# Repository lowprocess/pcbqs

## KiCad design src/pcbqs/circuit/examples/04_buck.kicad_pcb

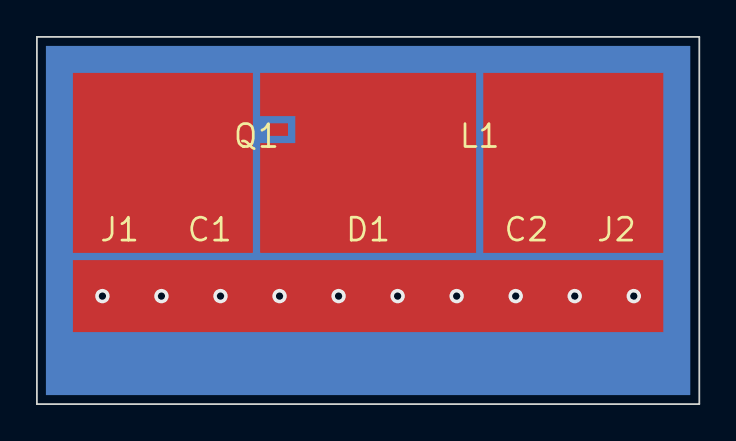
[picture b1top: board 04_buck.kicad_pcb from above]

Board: 2 copper layers, 36.8 x 20.4 mm, 7 parts (0 on the bottom side), 4 nets, no tracks yet.

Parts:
C1: 22u; C_1210_3225Metric
C2: 47u; C_1210_3225Metric
D1: D; D_SMA
J1: supply; SolderWirePad_1x02_SMD_3x3mm
J2: load 2.5; SolderWirePad_1x02_SMD_3x3mm
L1: 22uH; L_7.3x7.3_H4.5
Q1: MOSFET; SO-8FL_5x6mm

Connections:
GND: C1.2, C2.2, D1.2 (A), J1.2, J2.2
in: C1.1, J1.1, Q1.1 (D)
out: C2.1, J2.1, L1.2
sw: D1.1 (K), L1.1, Q1.2 (S)

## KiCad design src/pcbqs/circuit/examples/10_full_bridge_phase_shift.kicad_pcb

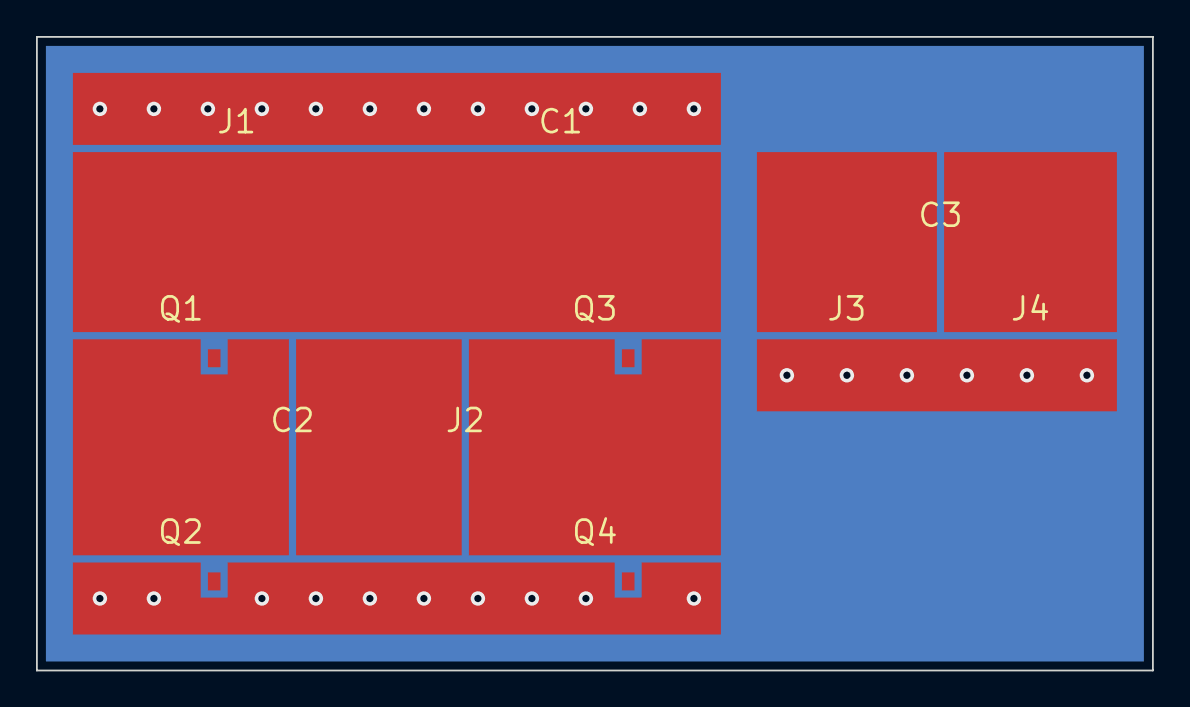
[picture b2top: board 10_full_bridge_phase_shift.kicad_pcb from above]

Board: 2 copper layers, 62.0 x 35.2 mm, 11 parts (0 on the bottom side), 7 nets, no tracks yet.

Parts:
C1: 47u; C_1210_3225Metric
C2: 100n; C_1210_3225Metric
C3: 130.3n; C_1210_3225Metric
J1: supply; SolderWirePad_1x02_SMD_3x3mm
J2, J3: coil 24uH; SolderWirePad_1x02_SMD_3x3mm
J4: load 6.3; SolderWirePad_1x02_SMD_3x3mm
Q1, Q2, Q3, Q4: MOSFET; SO-8FL_5x6mm

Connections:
GND: C1.2, J1.2, J3.2, J4.2, Q2.2 (S), Q4.2 (S)
a: C2.1, Q1.2 (S), Q2.1 (D)
b: J2.2, Q3.2 (S), Q4.1 (D)
in: C1.1, J1.1, Q1.1 (D), Q3.1 (D)
r: C3.2, J4.1
s: C3.1, J3.1
t: C2.2, J2.1
